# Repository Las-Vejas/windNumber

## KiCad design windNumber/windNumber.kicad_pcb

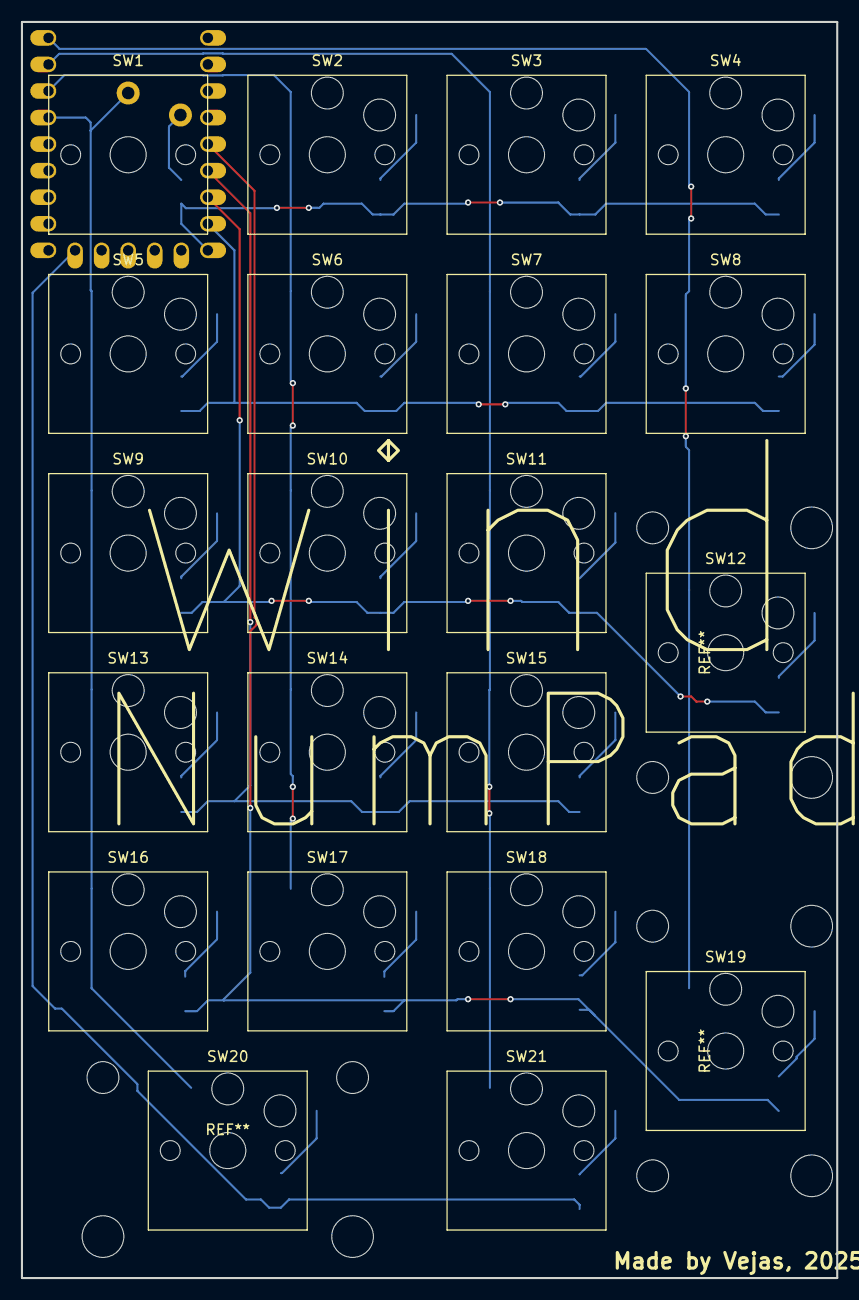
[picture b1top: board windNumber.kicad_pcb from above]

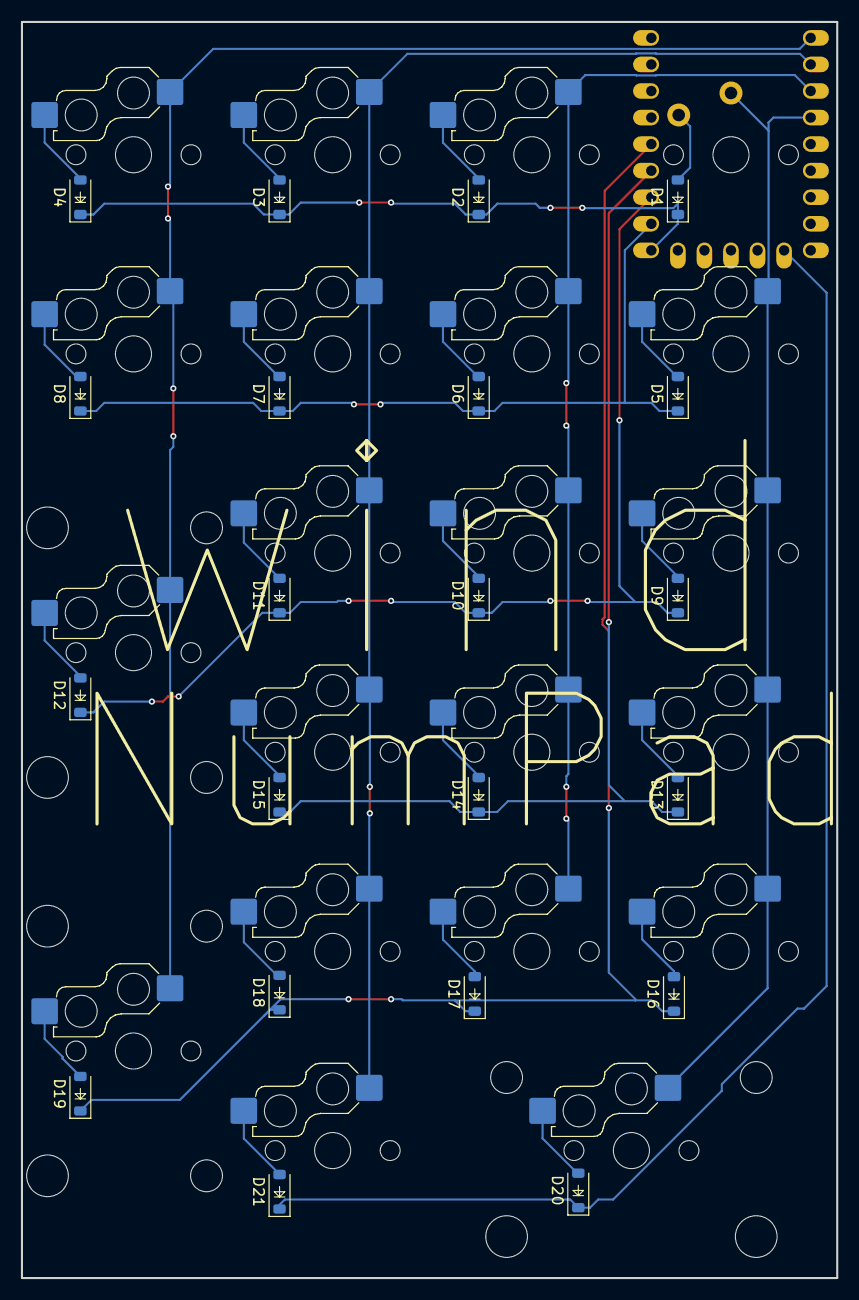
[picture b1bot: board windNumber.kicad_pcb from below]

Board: 2 copper layers, 78.0 x 120.1 mm, 43 parts (22 on the bottom side), 31 nets.

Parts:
D1, D2, D3, D4, D5, D6, D7, D8, D9, D10, D11, D12, D13, D14, D15, D16, D17, D18, D19, D20, D21: D_Small_Filled; D_SOD-123
SW1: SW_Push_45deg; Choc_V1_1.00u
SW2, SW3, SW4, SW5, SW6, SW7, SW8, SW9, SW10, SW11, SW13, SW14, SW15, SW16, SW17, SW18, SW21: SW_Push_45deg; Hotswap_Choc_V1_1.00u
SW12, SW19: SW_Push_45deg; Hotswap_Choc_V1_2.00u_90deg
SW20: SW_Push_45deg; Hotswap_Choc_V1_2.00u
U1: RP2040_Zero

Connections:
unnamed: D1.2 (A), SW1.2
unnamed: D2.2 (A), SW2.2
unnamed: D3.2 (A), SW3.2
unnamed: D4.2 (A), SW4.2
unnamed: D5.2 (A), SW5.2
unnamed: D6.2 (A), SW6.2
unnamed: D7.2 (A), SW7.2
unnamed: D8.2 (A), SW8.2
unnamed: D9.2 (A), SW9.2
unnamed: D10.2 (A), SW10.2
unnamed: D11.2 (A), SW11.2
unnamed: D12.2 (A), SW12.2
unnamed: D13.2 (A), SW13.2
unnamed: D14.2 (A), SW14.2
unnamed: D15.2 (A), SW15.2
unnamed: D16.2 (A), SW16.2
unnamed: D17.2 (A), SW17.2
unnamed: D18.2 (A), SW18.2
unnamed: D19.2 (A), SW19.2
unnamed: D20.2 (A), SW20.2
unnamed: D21.2 (A), SW21.2
c1: SW1.1, SW5.1, SW9.1, SW13.1, SW16.1, SW20.1, U1.4 (3)
c2: SW2.1, SW6.1, SW10.1, SW14.1, SW17.1, U1.3 (2)
c3: SW3.1, SW7.1, SW11.1, SW15.1, SW18.1, SW21.1, U1.2 (1)
c4: SW4.1, SW8.1, SW12.1, SW19.1, U1.1 (0)
r1: D1.1 (K), D2.1 (K), D3.1 (K), D4.1 (K), U1.15 (14)
r2: D5.1 (K), D6.1 (K), D7.1 (K), D8.1 (K), U1.16 (15)
r3: D9.1 (K), D10.1 (K), D11.1 (K), D12.1 (K), U1.17 (26)
r4: D13.1 (K), D14.1 (K), D15.1 (K), U1.18 (27)
r5: D16.1 (K), D17.1 (K), D18.1 (K), D19.1 (K), U1.19 (28)
r6: D20.1 (K), D21.1 (K), U1.10 (9)

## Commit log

2025-10-08 pcb stuff
